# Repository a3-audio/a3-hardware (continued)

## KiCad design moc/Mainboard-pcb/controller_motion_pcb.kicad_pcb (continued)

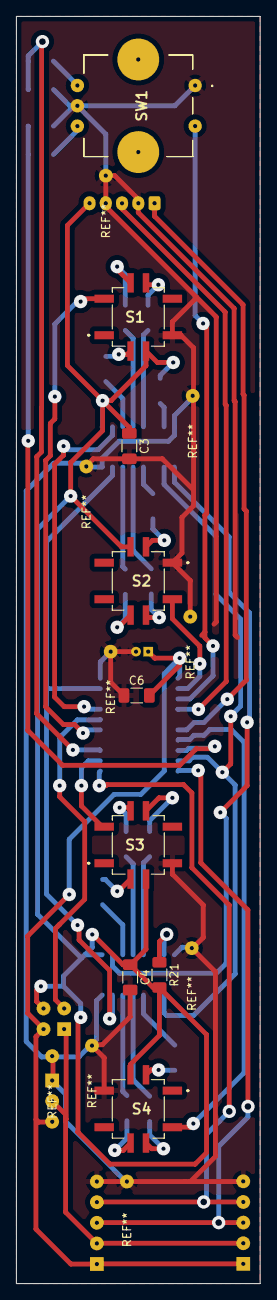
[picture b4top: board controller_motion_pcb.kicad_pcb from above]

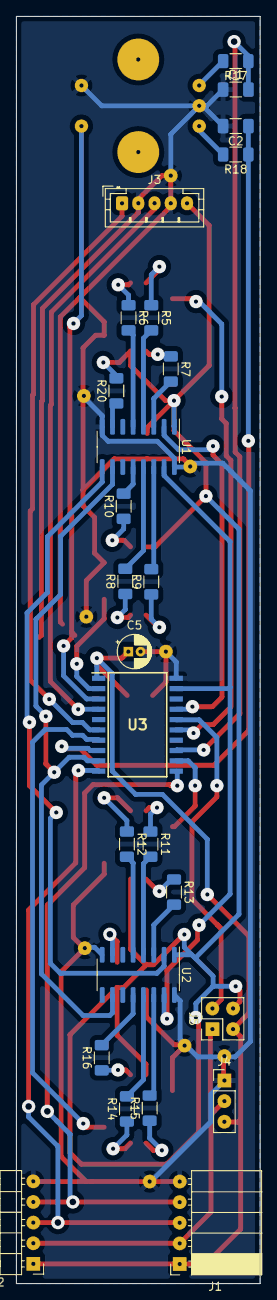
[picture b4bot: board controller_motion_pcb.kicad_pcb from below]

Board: 2 copper layers, 30.0 x 156.0 mm, 35 parts (26 on the bottom side), 48 nets.

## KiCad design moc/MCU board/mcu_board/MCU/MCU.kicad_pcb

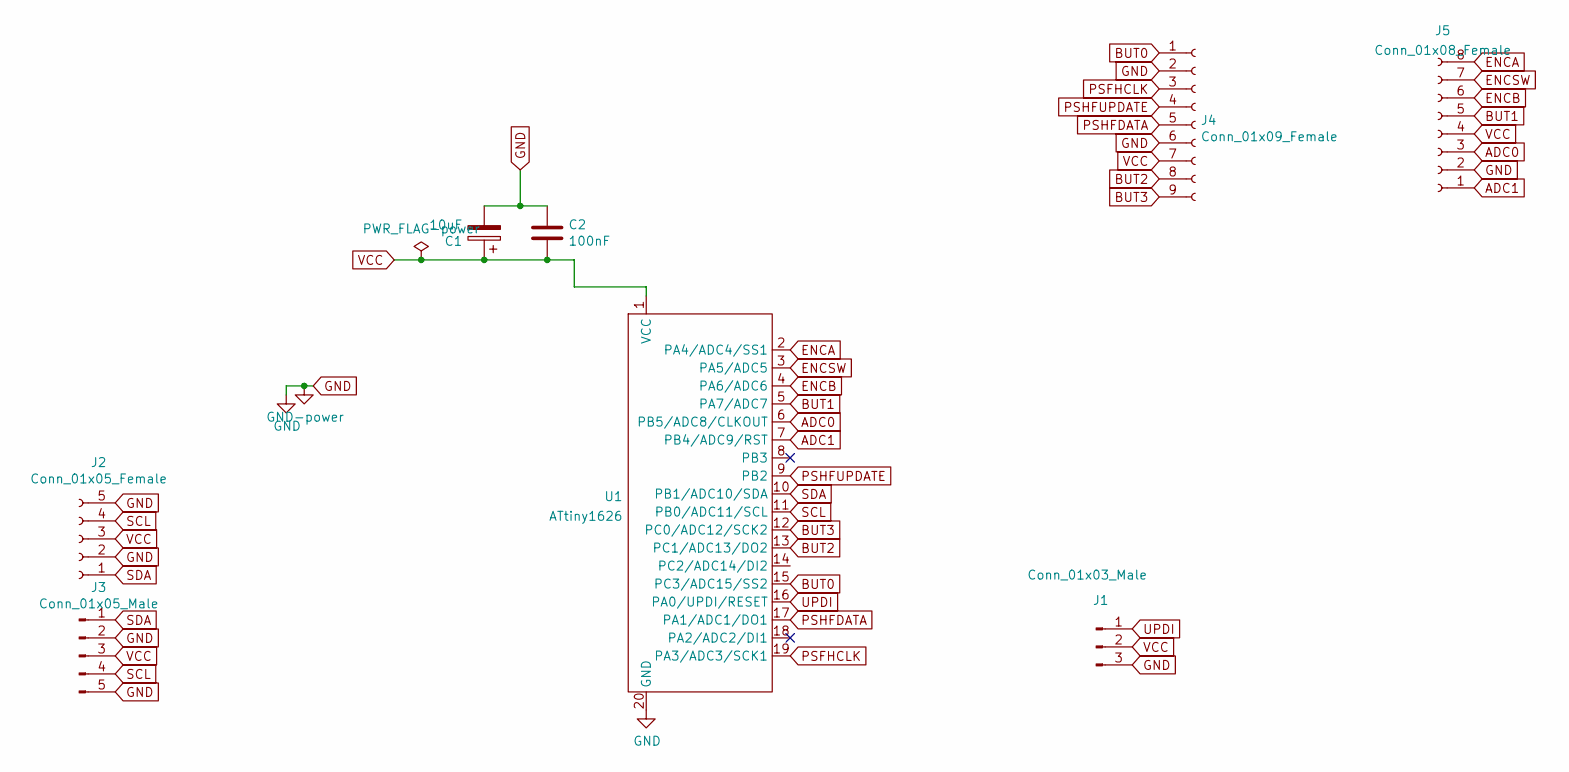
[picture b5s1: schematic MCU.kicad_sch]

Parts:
C1: 10uF; CP_Radial_D4.0mm_P1.50mm
C2: 100nF; C_1206_3216Metric_Pad1.33x1.80mm_HandSolder
J1: Conn_01x03_Male; PinHeader_1x03_P2.54mm_Vertical
J2: Conn_01x05_Female; PinSocket_1x05_P2.54mm_Horizontal
J3: Conn_01x05_Male; PinHeader_1x05_P2.54mm_Horizontal
J4: Conn_01x09_Female; Header-01x09-p2.54-selfsolder
J5: Conn_01x08_Female; PinHeader_1x08_P2.54mm_Vertical
U1: ATtiny1626; SOIC127P1030X265-20N

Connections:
ADC0: J5.3, U1.6 (PB5/ADC8/CLKOUT)
ADC1: J5.1, U1.7 (PB4/ADC9/RST)
BUT0: J4.1, U1.15 (PC3/ADC15/SS2)
BUT1: J5.5, U1.5 (PA7/ADC7)
BUT2: J4.8, U1.13 (PC1/ADC13/DO2)
BUT3: J4.9, U1.12 (PC0/ADC12/SCK2)
ENCA: J5.8, U1.2 (PA4/ADC4/SS1)
ENCB: J5.6, U1.4 (PA6/ADC6)
ENCSW: J5.7, U1.3 (PA5/ADC5)
GND: C1.2, C2.1, J1.3, J2.2, J2.5, J3.2, J3.5, J4.2, J4.6, J5.2, U1.20 (GND)
PSFHCLK: J4.3, U1.19 (PA3/ADC3/SCK1)
PSHFDATA: J4.5, U1.17 (PA1/ADC1/DO1)
PSHFUPDATE: J4.4, U1.9 (PB2)
SCL: J2.4, J3.4, U1.11 (PB0/ADC11/SCL)
SDA: J2.1, J3.1, U1.10 (PB1/ADC10/SDA)
UPDI: J1.1, U1.16 (PA0/UPDI/RESET)
VCC: C1.1, C2.2, J1.2, J2.3, J3.3, J4.7, J5.4, U1.1 (VCC)

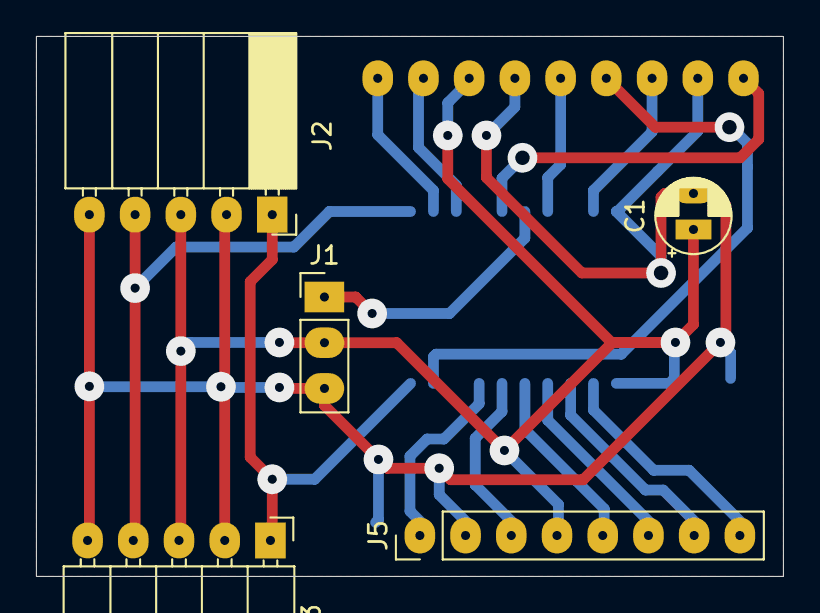
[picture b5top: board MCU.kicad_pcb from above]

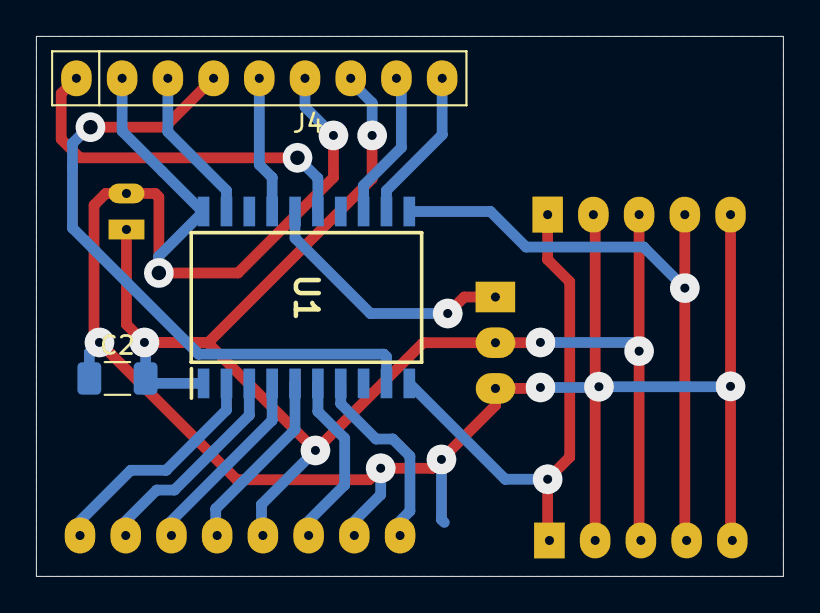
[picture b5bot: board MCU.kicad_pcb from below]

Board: 2 copper layers, 41.5 x 30.0 mm, 8 parts (3 on the bottom side), 17 nets.

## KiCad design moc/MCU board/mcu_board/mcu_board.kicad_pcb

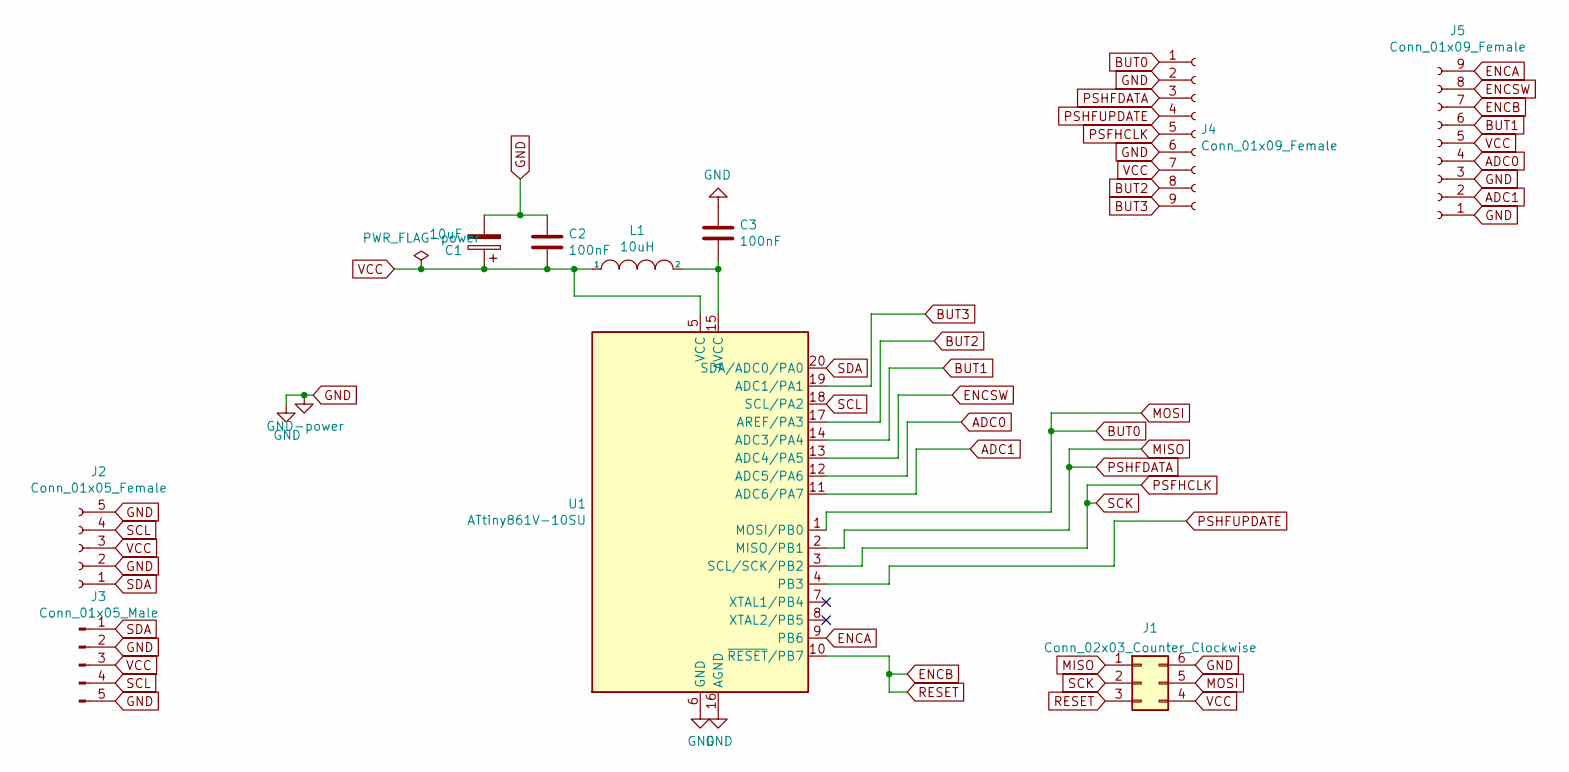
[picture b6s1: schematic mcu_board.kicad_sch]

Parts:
C1: 10uF; CP_Radial_D4.0mm_P1.50mm
C2, C3: 100nF; C_1206_3216Metric_Pad1.33x1.80mm_HandSolder
J1: Conn_02x03_Counter_Clockwise; ICSP_Header_P2.54_SelfSolder
J2: Conn_01x05_Female; PinSocket_1x05_P2.54mm_Horizontal
J3: Conn_01x05_Male; PinHeader_1x05_P2.54mm_Horizontal
J4, J5: Conn_01x09_Female; Header-01x09-p2.54-selfsolder
L1: 10uH; L_1206_3216Metric_Pad1.22x1.90mm_HandSolder
U1: ATtiny861V-10SU; SOIC-20W_7.5x12.8mm_P1.27mm

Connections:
ADC0: J5.4, U1.12 (ADC5/PA6)
ADC1: J5.2, U1.11 (ADC6/PA7)
BUT0: J1.5, J4.1, U1.1 (MOSI/BUT0)
BUT1: J5.6, U1.14 (ADC3/PA4)
BUT2: J4.8, U1.17 (AREF/PA3)
BUT3: J4.9, U1.19 (ADC1/PA1)
ENCA: J5.9, U1.9 (PB6)
ENCB: J1.3, J5.7, U1.10 (~RESET/PB7)
ENCSW: J5.8, U1.13 (ADC4/PA5)
GND: C1.2, C2.1, C3.1, J1.6, J2.2, J2.5, J3.2, J3.5, J4.2, J4.6, J5.1, J5.3, U1.6 (GND), U1.16 (AGND)
MISO: J1.1, J4.3, U1.2 (MISO/BUT1)
unnamed: C3.2, L1.2, U1.15 (AVCC)
PSFHCLK: J1.2, J4.5, U1.3 (SCL/SCK/BUT2)
PSHFUPDATE: J4.4, U1.4 (BUT3)
SCL: J2.4, J3.4, U1.18 (SCL/PA2)
SDA: J2.1, J3.1, U1.20 (SDA/ADC0/PA0)
VCC: C1.1, C2.2, J1.4, J2.3, J3.3, J4.7, J5.5, L1.1, U1.5 (VCC)

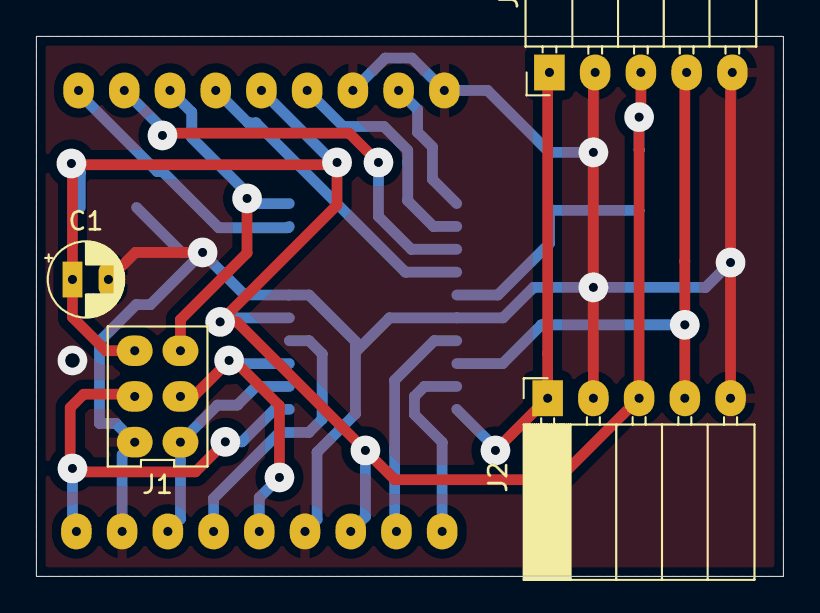
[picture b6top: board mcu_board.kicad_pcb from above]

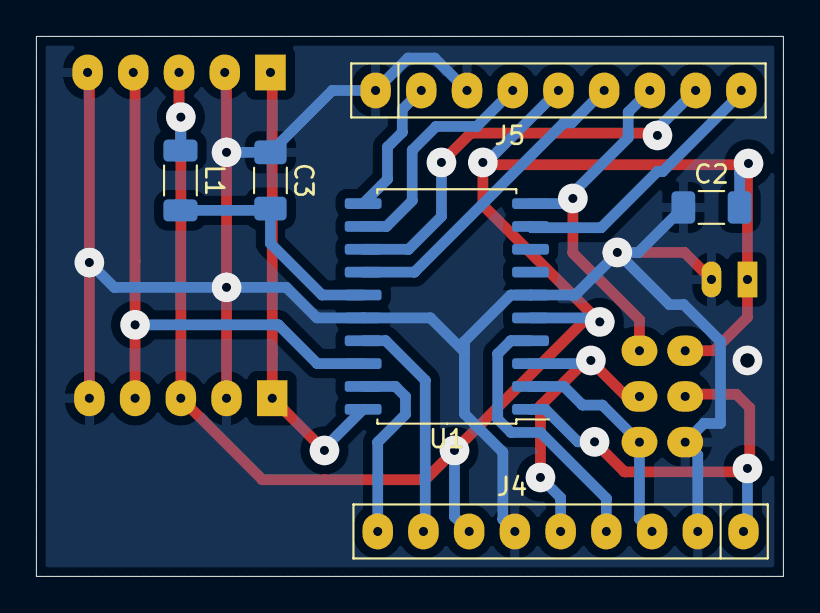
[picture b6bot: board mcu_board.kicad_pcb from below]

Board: 2 copper layers, 41.5 x 30.0 mm, 10 parts (6 on the bottom side), 17 nets.

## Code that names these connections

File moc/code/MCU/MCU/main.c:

/*
* MCU.c
*
* Created: 23/01/2022 00:13:26
* Author : Felix Dahmen

Header (NEW)
GND 11  GND 12  VCC 14  10  13  9
 -  PA7  -  PA6  -  PA4 PB7 PA5 PB6
    AD6     AD5     AD3 RS  AD4  -

AD1 ARE         SCL  -  DO   -  SDA
PA1 PA3  -   -  PB2 PB3 PB1  -  PB0
 19 17  VCC GND 3   4   2   GND 1

Header (OLD)
GND 11  GND 12  VCC 14  10  13  9
-  PA7  -  PA6  -  PA4 PB7 PA5 PB6
   AD6     AD5     AD3 RS  AD4  -

AD1 ARE         SCL  -  SDA  -  DO
PA1 PA3  -   -  PB2 PB3 PB0  -  PB1
 19 17  VCC GND 3   4   1   GND  2


COM Interface (OLD)
SDA GND VCC SCL GND



*/

#define F_CPU 8E6

#define DEVICE_ADDRESS	(4)

#include <util/delay.h>
#include <avr/io.h>
#include "main.h"
#include <avr/interrupt.h>
#include "usitwislave.h"
#include <stdint.h>
#include <avr/sleep.h>

#define SETBIT(ADDRESS,BIT) (ADDRESS |= (1<<BIT))
#define CLEARBIT(ADDRESS,BIT) (ADDRESS &= ~(1<<BIT))
#define FLIPBIT(ADDRESS,BIT) (ADDRESS ^= (1<<BIT))
#define CHECKBIT(ADDRESS,BIT) (ADDRESS & (1<<BIT))

#define PSHFDATA 1  //B O
#define PSHFCLK 2  //B O
#define PSHFUPDATE 3  //B O

#define PENCA 6  //B I
#define PENCB 7  //B I
#define PENSCW 5  //A I

#define PSDA PA0  //A XXX
#define PSCL PA2  //A

#define BUT0 0  //B I
#define BUT1 4  //A  I
#define BUT2 3  //A I
#define BUT3 1  //A I

#define PADC0 6  //A I
#define PADC1 7  //A I
#define N_ADC_BUFFER 32
uint8_t iAdcBuffer=0;
uint32_t adcval0;
uint16_t adcvalBuffer0[N_ADC_BUFFER];
static uint8_t test=0;

#define func(A) writeSPI4(A)

#define RED PA1
#define BLUE PA3
#define GREEN PA4

uint8_t timer1test=0;

#define RGB_COLORS (sizeof(rgb_r)/sizeof(rgb_r[0])) //must be multiple of 4
#define RGB_LEVELS 15 //number of brightness levels

typedef enum {
	I2C_REQUEST_ADC0=0x63,
	I2C_REQUEST_ADC1=0x95,
	I2C_IDLE=0
	}i2c_state;

volatile i2c_state i2cState=I2C_IDLE;

volatile uint8_t rgb_counter=2;
volatile uint8_t rgb_brightness=5;
volatile uint8_t rgb_color=0;


int intr_count=0;
int sec=0;

ISR (TIMER0_OVF_vect)      //Interrupt vector for Timer0
{
	
	//rgb_out();
	//PORTB^=(1<<RED); //toggling the LED
	//uint16_t start_val= - 4; //5000us/256us/200Hz
	//TCNT0H=(uint8_t)(start_val>>8);
	
			if((timer1test++)&1)
			PORTB|=(1<<PB6);
			else
			CLEARBIT(PORTB,PB6);
	TCNT0L=-80;
}
ISR (TIMER1_OVF_vect)      //Interrupt vector for Timer0
{
	
	//rgb_out();
	//PORTB^=(1<<RED); //toggling the LED
	//uint16_t start_val= - 4; //5000us/256us/200Hz
	//TCNT0H=(uint8_t)(start_val>>8);
	
	if((timer1test++)&1)
	PORTB|=(1<<PB6);
	else
	CLEARBIT(PORTB,PB6);
	TCNT1=-80;
	//set_sleep_mode(SLEEP_MODE_ADC);
}

ISR (ADC_vect)
{	
	//set_sleep_mode(SLEEP_MODE_IDLE);
	uint16_t adcval_temp=ADCL;
	adcval_temp|=(ADCH<<8);
	adcval0+=adcval_temp;
	adcval0-=adcvalBuffer0[(iAdcBuffer+1)%N_ADC_BUFFER];
	iAdcBuffer++;
	iAdcBuffer%=N_ADC_BUFFER;
	adcvalBuffer0[iAdcBuffer]=adcval_temp;
	ADCSRA|=(1<<ADIF);
	
	//adcval|=ADCH;
	//uint8_t val=adcval/(UINT16_MAX/14)+2;
}

void timer0_setup()
{

	
	TCCR0A=0x00;   //Normal mode 8bit counter
	TCCR0B=0x00;
	TCCR0B |= (1<<CS00);   //prescaling with 1024
	TCNT0L=-10;
	TIMSK|=(1<<TOIE0); //enabling timer0 interrupt

}

void timer1_setup()
{

	TCCR1A=0x00;   //Normal mode 8bit counter
	TCCR1B=0x00;
	TCCR1B |= (1<<CS11);   //prescaling with 2
	TCNT1=-10;
	TIMSK|=(1<<TOIE1); //enabling timer0 interrupt
}
/*
ADCSRA
ADEN: ADC Enable
ADSC starts conversion
This bit stays high as long as the conversion is in progress
If a different data channel is selected while a conversion is in
progress, the ADC will finish the current conversion before performing the channel change.
ADPS2:0: bits
sample frequency 50-200khz
A normal conversion takes 13 ADC clock cycles.
ADIF: ADC Interrupt Flag
ADIE: ADC Interrupt Enable

ADCSRB
MUX5:0 channel select
REFS2:0 reference select


After the conversion is complete (ADIF is high), the conversion result can be found in the ADC
Result Registers (ADCL, ADCH).

ADMUX
REFS1:REFS0 0 0 heisst Vcc ref
MUX4:0 0-10 geben input pin PA0-PA7;PB4-PB7

ADCL and ADCH  The ADC Data Register
*/
void adc_setup(){
	ADMUX =
	(0 << ADLAR) |     // left shift result
	(0 << REFS1) |     // Sets ref. voltage to VCC, bit 1
	(0 << REFS0) |     // Sets ref. voltage to VCC, bit 0
	//MUX	0-6		a0 a1 a2 a4 a5 a6 a7 
	//		7-10	b4 b5 b6 b7
	(0 << MUX4)  |  (0 << MUX3)  |	(0 << MUX2)  |	(0 << MUX1)  |(1 << MUX0);       

	ADCSRA =
	(1 << ADEN)  |     // Enable ADC
	(1 << ADIE)  |     // ADC Interrupt Enable
	(1<<ADATE)	  |    // Auto triger enable this time timer 1 overflow
	(0 << ADPS2) |	(0 << ADPS1) |	(0 << ADPS0);	// prescaler system clock 
													//0,1:	2	2:	4	3:	8	4:	16
													//5:	32	6:	64	7:	128 
	
	ADCSRB=(0<<MUX5)|
			(1<<ADTS2)	|
			(1<<ADTS1)	|
			(0<<ADTS0);
}
void rgb_out(){
	uint8_t r=rgb_r[rgb_color]*rgb_brightness;
	uint8_t g=rgb_g[rgb_color]*rgb_brightness;
	uint8_t b=rgb_b[rgb_color]*rgb_brightness;
	uint8_t mask=(1<<RED)|(1<<BLUE)|(1<<GREEN);
	uint8_t PORT_temp=((PORTA&~mask));
	PORT_temp|=((r>rgb_counter)<<RED)|((g>rgb_counter)<<GREEN)|((b>rgb_counter)<<BLUE);
	PORTA=PORT_temp;
	rgb_counter++;
	rgb_counter = rgb_counter % RGB_LEVELS;

}


uint8_t sendthis[]={1,2,3,4,5};
uint8_t regs[4] = { 4, 8, 16, 32 };
uint8_t currentReg = 0;


static void request(volatile uint8_t input_buffer_length, const uint8_t *input_buffer,
uint8_t *output_buffer_length, uint8_t *output_buffer) {
	// the number of bytes to be returned to the master
	*output_buffer_length = 2;
	//output_buffer[0] = 55;
	uint32_t adcValTemp=0;
	if(input_buffer_length>0){
		switch (input_buffer[0])
		{
			case I2C_REQUEST_ADC0:
				
				adcValTemp=(adcval0>>5);
				output_buffer[0] = (adcValTemp>>8)&0xFF;
				output_buffer[1] = adcValTemp&0xFF;
			break;
			default:
				output_buffer[0]=66;
				output_buffer[1]=66;//input_buffer_length;//input_buffer[0];
			break;
				//output_buffer[1]=-1;
		}
		
		
	}else{
		*output_buffer_length=2;
		output_buffer[0]=88;
		output_buffer[1]=88;
	}
	
	// the data to be returned
	//(0x11);//regs[currentReg];
	
	// send the next reg next time
	//currentReg++;
	//if (currentReg > sizeof(regs)) {
		//currentReg = 0;
	//}
	//return;
	// If you have multiple bytes, return each one:
	//output_buffer[0] = regs[currentReg];
	//output_buffer[1] = regs[currentReg + 1];

	// If you want to send a single value larger than one byte, you will need to split it into bytes,
	// send and then reassemble at the master. Maximum size in the library default is 32 bytes
	// You can increase this in usitwislave.h
	//uint16_t val = 256;
	///*output_buffer_length = 2;
	//output_buffer[0] = (val >> 8) & 0xFF;
	//output_buffer[1] = val & 0xFF;
}

void idle() {
	// whatever you need to do, flash LEDs, etc.
}
/*
void sleep_enable()
{
	MCUCR|=(1<<SM0);      // enabling sleep mode and powerdown sleep mode
	MCUCR|= (1<<SE);     //Enabling sleep enable bit
	//__asm__ __volatile__ ( "sleep" "\n\t" :: ); //Sleep instruction to put controller to sleep
	//controller stops executing instruction after entering sleep mode
}
void sleep_disable(){
	MCUCR&=~(1<<SE);
}*/

int main(void)
{
	DDRB|=(1<<PB6);
	adc_setup();
	timer1_setup();
	usi_twi_slave(DEVICE_ADDRESS, 1, request, ((void*)0));
	sei();
	while (1);
	
}

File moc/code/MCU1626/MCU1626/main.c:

/*
* MCU1626.c
*
* Created: 23/02/2022 13:06:16
* Author : tirii
*/
#include "main.h"


/*
(MALE)
1	 2	 3	 4	 5
GND	SDC	SDA	UPD	VCW
--- PB0	PB1

10	 9	 8	 7	 6	 4	 3	 2
SDA	SHU	ENB	BU3	AD1	AD0	ESW	BU1
PB1	PB2	PB3	PB4	PB5	PA6	PA5	PA4



11	 12	 13	 15	 16	 17	 19		 1	 2	 3
SCL	BU2	ENA	BU0	UPD	SHD	SHC		VCW	UPD	GND
PB0	PC0	PC1	PC3	PA0	PA1	PA3
*/

uint16_t i2c_responseValue;
volatile uint8_t counter=0;
volatile uint8_t counterNew=0;

//ADC sample is ready
ISR(ADC0_SAMPRDY_vect){
	uint8_t tL=ADC0_SAMPLEL;
	uint8_t tH=ADC0_SAMPLEH;
	ADC0.INTFLAGS|=ADC_RESOVR_bm;
	adc_setValue(((uint16_t)(tH<<8))|tL);
}

//Led snet interrupt
//updates the shift register
ISR(SPI0_INT_vect){
	if(SPI0.INTFLAGS&SPI_TXCIF_bm){
		BIT_SET(LED_SHU_PT.OUTSET,LED_SHU_BP);//ACK BIT ON
		BITMASK_SET(SPI0.INTFLAGS,SPI_TXCIF_bm);
		BITMASK_CLEAR(SPI0.INTCTRL,SPI_TXCIE_bm);
		BIT_SET(LED_SHU_PT.OUTCLR,LED_SHU_BP);//ACK BIT OFF
		
	}
}

//LED Shift counter
//clock cycle 3ms/255
ISR(TCA0_OVF_vect){
	TCA0.SINGLE.INTFLAGS|=TCA_SINGLE_OVF_bm;//clear interrupt flag
	ledEvent rgbEvent=led_getNextEvent();
	TCA0.SINGLE.PER=rgbEvent.time;
	led_shiftSend(rgbEvent.shiftVal);
}
//100us
ISR(TCB0_INT_vect){
	TCB0.INTFLAGS|=TCB_CAPT_bm;
	counterNew++;
	counterNew%=10;
}

ISR(TWI0_TWIS_vect)
{
	if(TWI0.SSTATUS & TWI_APIF_bm)					//Address match/stop interrupt
	{
		if (TWI0.SSTATUS & TWI_COLL_bm)
		{
			TWI0.SSTATUS |= TWI_COLL_bm;			//Clear Collision flag
			TWI0_SCTRLB = TWI_SCMD_COMPTRANS_gc;	//complete transaction
			return;
		}
		if(TWI0.SSTATUS & TWI_AP_bm)
		TWI0_SCTRLB = TWI_SCMD_RESPONSE_gc;		//Send ACK after address match
		else
		TWI0_SCTRLB = TWI_SCMD_COMPTRANS_gc;	//complete transaction after Stop
	}
	
	if(TWI0.SSTATUS & TWI_DIF_bm)					//Data interrupt
	{
		if(TWI0.SSTATUS & TWI_DIR_bm)
		{
			i2cResponseStrct resp = i2c_get_response();
			switch(resp.response){
				case sendADC0:
				if(resp.index==0){
				i2c_responseValue=adc_getValue(0);
				TWI0.SDATA = (uint8_t)i2c_responseValue;
				}else
				TWI0.SDATA =(uint8_t)(i2c_responseValue>>8);
				break;
				case sendADC1:
				if(resp.index==0){
				i2c_responseValue=adc_getValue(1);
				TWI0.SDATA = (uint8_t)i2c_responseValue;
				}else
				TWI0.SDATA =(uint8_t)(i2c_responseValue>>8);
				break;
				case sendENC:
				if(resp.index==0){
				i2c_responseValue=enc_getValue();
				TWI0.SDATA = (uint8_t)i2c_responseValue;
				}else
				TWI0.SDATA =(uint8_t)(i2c_responseValue>>8);
				break;
				case sendBUT:
				TWI0.SDATA=but_getValue();
				default:
				TWI0.SDATA = 11;
				break;
			}
			// spi_get_response();						//Transmit data for Master to read
			
			TWI0_SCTRLB = TWI_SCMD_RESPONSE_gc;
		}
		else
		{
			TWI0_SCTRLB = TWI_SCMD_RESPONSE_gc;
			uint8_t t=TWI0.SDATA;
			i2c_set_message(t);
			//nnn=t;
			//Receive data written by Master
		}
	}
}


int main(void)
{	ccp_write_io((void *) & (CLKCTRL.MCLKCTRLB), 0); //protected write to disable prescaler of CPU clock
	debug_init();
	timer0_init();
	timer1_init();
	i2c_init();
	led_init();
	but_init();
	adc_init();
	enc_init();
	sei();
	
	while (1)
	{
		if(counter!=counterNew){
			counter=counterNew;
			switch(counter){
				case 0:;//strange error but the semicolon has to be there
				i2cOrderStrct	a=i2c_get_order();
				if(a.order>-1){
					uint8_t		val=a.msg[2];
					val*=2;
					uint16_t	angle=(a.msg[1]<<7)|(a.msg[0]&0xFF);
					switch (a.order)
					{
						case ordRgb0:
						led_updateRGB(0,angle,val);
						break;
						
						case ordRgb1:
						led_updateRGB(1,angle,val);
						break;
						
						case ordRgb2:
						led_updateRGB(2,angle,val);
						break;
						
						case ordRgb3:
						led_updateRGB(3,angle,val);
						break;
						default:
						break;
					}
					
				}
				
				break;
				case 1:
				enc_start();
				break;
				case 2:
				adc_start();
				break;
				case 3:
				but_start();
				break;
				case 6:
				adc_start();
				break;
				default:
				break;
			}
		}
	}
}





/*
if(counter==0||counter==64||counter==128||counter==192){
if(BIT_CHECK(PORTC.IN,PIN3_bp)){
BIT_CLEAR(buttons[0].sample,buttonCount);
}else{
BIT_SET(buttons[0].sample,buttonCount);
}
if(buttons[0].state==STATE_BUT_PRESSED&&buttons[0].sample==STATE_BUT_RELEASED){
buttons[0].state=STATE_BUT_RELEASED;
leds[0]=hsvtoRGB(tLed0Count,255);
}else
if(buttons[0].state==STATE_BUT_RELEASED&&buttons[0].sample==STATE_BUT_PRESSED){
buttons[0].state=STATE_BUT_PRESSED;
tLed0Count+=10;
tLed0Count%=360;
leds[0]=hsvtoRGB(100,255);
}

//... andere buttons
buttonCount=(buttonCount+1)&0b00000111;
}else*/

/*else{



enc_delta=0;
if(encoder_val!=tLed0Count){
tLed0Count+=10;
encoder_val=tLed0Count;
leds[0]=hsvtoRGB(tLed0Count,255);



}
}*/

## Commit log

2021-11-18 int hardware
2021-11-18 Move hardware from Ambijocky to the hardware submodule.
2021-11-18 rename mic/ to mix/
2021-11-18 clean up
2021-12-09 library path corrected
2021-12-09 noch eine
2021-12-12 MCU and Controller board done
2021-12-15 Plots ready
2022-01-27 edit
2022-02-06 first protoype
2022-03-09 split PCB Board
    That's the final version for the split PCB board with 3 PCB Boards
2022-03-20 hardware io funzt
2022-05-14 ready to publish
2022-05-16 rename a folder
2022-05-16 cc-by-sa / create pdf files
2022-05-18 A³ Mix draft license ohl-s
2022-05-18 ohl-s ready
2022-05-20 ohl-s ready - get license info with 'reuse lint'
2022-05-24 typo
2022-06-01 add readme
